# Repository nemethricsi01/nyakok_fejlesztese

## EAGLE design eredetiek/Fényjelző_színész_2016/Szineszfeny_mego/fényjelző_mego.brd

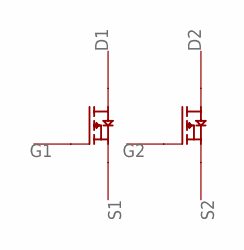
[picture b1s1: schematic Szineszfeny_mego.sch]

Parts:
D1, D2: PADSMD_KICSI; PAD_SMD_KICSI
G1, G2: PADSMD_KICSI; PAD_SMD_KICSI
S1, S2: PADSMD_KICSI; PAD_SMD_KICSI
U$1: AP2625GY-HF-3SOT26; SOT26

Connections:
unnamed: G1.P$4, U$1.P$1 (G)
unnamed: S1.P$4, U$1.P$5 (S)
unnamed: D1.P$4, U$1.P$6 (D)
unnamed: G2.P$4, U$1.P$3 (G)
unnamed: S2.P$4, U$1.P$2 (S)
unnamed: D2.P$4, U$1.P$4 (D)

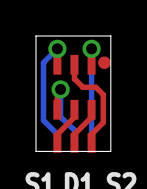
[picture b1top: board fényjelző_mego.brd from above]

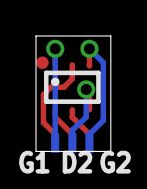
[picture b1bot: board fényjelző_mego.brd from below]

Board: 2 copper layers, 4.2 x 6.4 mm, 7 parts (3 on the bottom side), 6 nets.

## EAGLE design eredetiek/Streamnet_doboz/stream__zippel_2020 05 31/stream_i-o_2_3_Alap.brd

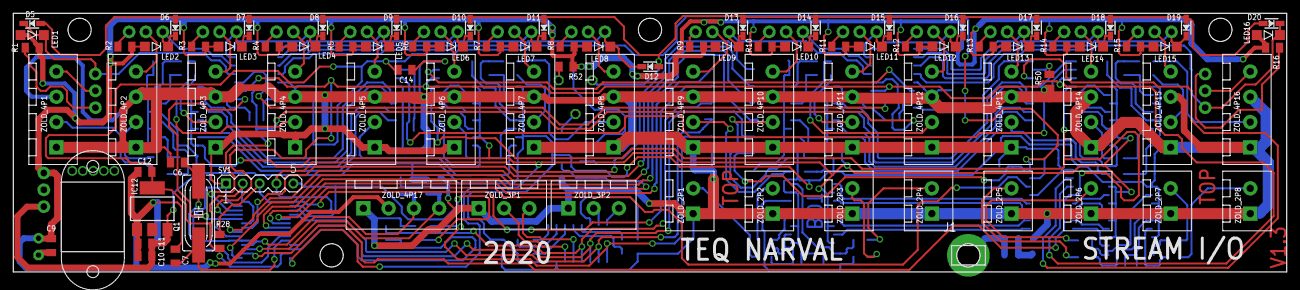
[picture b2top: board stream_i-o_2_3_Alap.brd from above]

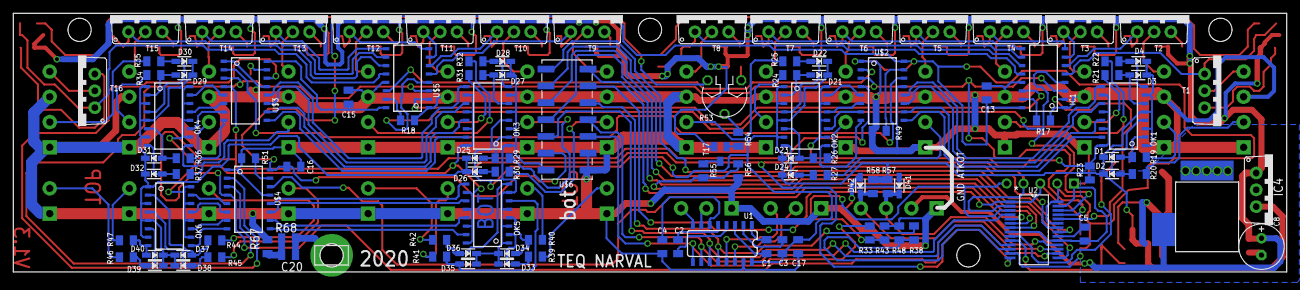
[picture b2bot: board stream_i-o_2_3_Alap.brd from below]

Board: 2 copper layers, 192.0 x 39.0 mm, 200 parts (110 on the bottom side), 174 nets.

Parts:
C1, C2, C3, C4: 1u; C0805
C5, C10, C11, C12: 10u; C0805
C6, C7: 22p; C0805
C8: 220u; E2,5-7
C9, C13, C14, C15, C16, C17, C20: 100n; C0805
D1, D2, D3, D4, D5, D6, D7, D8, D9, D10, D11, D12, D13, D14, D15, D16, D17, D18, D19, D20, D21, D22, D23, D24, D25, D26, D27, D28, D29, D30, D31, D32, D33, D34, D35, D36, D37, D38, D39, D40, D41, D42: 1N4148; SOD-323
DC1: DC_55/21
IC1: SCT21SOP16; SOP16
IC4: 7805TV; TO220V
IC12: LD117AS33TR; SOT223
J1: PIN1-2; 62221
LED1, LED2, LED3, LED4, LED5, LED6, LED7, LED8, LED9, LED10, LED11, LED12, LED13, LED14, LED15, LED16: RED; CHIPLED_1206
OK1, OK2, OK3, OK4, OK5, OK6: TLP281-4; MINI-FLAT-16
Q1: 20MHz; HC49UP
R1, R2, R3, R4, R5, R6, R7, R8, R9, R10, R11, R12, R13, R14, R15, R16: 6R8; R0805
R17, R18, R54, R55, R68: 10k; R0805
R19, R20, R21, R22, R24, R25, R26, R27, R29, R30, R31, R32, R34, R35, R36, R37, R39, R40, R41, R42, R43, R44, R45, R46, R47, R48, R49, R50, R51: 2k2; R0805
R23, R28, R33, R38: 1k; R0805
R52, R57, R58: 4k7; R0805
R53: 10k; PT-6
R56: 3k3; R0805
R67: 100; R0805
SV1: PROG; MA05-1
T1, T2, T3, T4, T5, T6, T7, T8, T9, T10, T11, T12, T13, T14, T15, T16: BD242; TO220V
T17: BC858; SOT23-BEC
U1: MAX232SOIC16; SO016
U2: PIC32MX250F128B-I_SS; SSOP28_MC
U$2, U$3, U$4, U$5: SCT21SOP16; SOP16
U$6: PIN_HEADER_2X7
ZOLD_2P1, ZOLD_2P2, ZOLD_2P3, ZOLD_2P4, ZOLD_2P5, ZOLD_2P6, ZOLD_2P7, ZOLD_2P8: ZOLD_KICSI_2P
ZOLD_3P1, ZOLD_3P2: ZOLD_KICSI_3P
ZOLD_4P1, ZOLD_4P2, ZOLD_4P3, ZOLD_4P4, ZOLD_4P5, ZOLD_4P6, ZOLD_4P7, ZOLD_4P8, ZOLD_4P9, ZOLD_4P10, ZOLD_4P11, ZOLD_4P12, ZOLD_4P13, ZOLD_4P14, ZOLD_4P15, ZOLD_4P16, ZOLD_4P17: ZOLD_KICSI_4P

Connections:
+3V3: C12.1, C13.1, C14.1, C15.1, C16.1, IC1.16, IC12.4, R28.2, SV1.2, U2.13, U2.23, U2.28, U$2.16, U$3.16, U$4.16, U$5.16, U$6.6B
+5V: C3.1, C10.1, C11.1, C17.1, D1.C, D2.C, D3.C, D4.C, D21.C, D22.C, D23.C, D24.C, D25.C, D26.C, D27.C, D28.C, D29.C, D30.C, D31.C, D32.C, D33.C, D34.C, D35.C, D36.C, D37.C, D38.C, D39.C, D40.C, IC4.3, IC12.3, OK1.1, OK1.3, OK1.5, OK1.7, OK2.1, OK2.3, OK2.5, OK2.7, OK3.1, OK3.3, OK3.5, OK3.7, OK4.1, OK4.3, OK4.5, OK4.7, OK5.1, OK5.3, OK5.5, OK5.7, OK6.1, OK6.3, OK6.5, OK6.7, R23.2, R57.2, R58.2, U1.16, U$6.7B
+12V: C8.+, C9.1, DC1.2, IC4.1, LED1.A, LED2.A, LED3.A, LED4.A, LED5.A, LED6.A, LED7.A, LED8.A, LED9.A, LED10.A, LED11.A, LED12.A, LED13.A, LED14.A, LED15.A, LED16.A, R1.2, R2.2, R3.2, R4.2, R5.2, R6.2, R7.2, R8.2, R9.2, R10.2, R11.2, R12.2, R13.2, R14.2, R15.2, R16.2, R52.2, T17.E, ZOLD_4P17.2
CHECK: U2.5, U$4.14
CLK: IC1.3, U2.25, U$2.3, U$3.3, U$4.3, U$5.3
D+: U2.21, U$6.3B
D-: U2.22, U$6.2B
GND: C4.2, C5.2, C6.1, C7.1, C8.-, C9.2, C10.2, C11.2, C12.2, C13.2, C14.2, C15.2, C16.2, C17.2, D41.A, D42.A, DC1.1, IC1.1, IC1.13, IC4.2, IC12.1, R17.1, R18.1, R43.1, R48.1, R49.1, R50.1, R51.1, R56.1, R67.2, SV1.1, U1.15, U2.8, U2.19, U2.27, U$2.1, U$2.13, U$3.1, U$3.13, U$4.1, U$4.13, U$5.1, U$5.13, U$6.6A, U$6.7A, ZOLD_2P1.1, ZOLD_2P2.1, ZOLD_2P3.1, ZOLD_2P4.1, ZOLD_2P5.1, ZOLD_2P6.1, ZOLD_2P7.1, ZOLD_2P8.1, ZOLD_3P1.1, ZOLD_3P2.1, ZOLD_4P1.1, ZOLD_4P1.3, ZOLD_4P2.1, ZOLD_4P2.3, ZOLD_4P3.1, ZOLD_4P3.3, ZOLD_4P4.1, ZOLD_4P4.3, ZOLD_4P5.1, ZOLD_4P5.3, ZOLD_4P6.1, ZOLD_4P6.3, ZOLD_4P7.1, ZOLD_4P7.3, ZOLD_4P8.1, ZOLD_4P8.3, ZOLD_4P9.1, ZOLD_4P9.3, ZOLD_4P10.1, ZOLD_4P10.3, ZOLD_4P11.1, ZOLD_4P11.3, ZOLD_4P12.1, ZOLD_4P12.3, ZOLD_4P13.1, ZOLD_4P13.3, ZOLD_4P14.1, ZOLD_4P14.3, ZOLD_4P15.1, ZOLD_4P15.3, ZOLD_4P16.1, ZOLD_4P16.3, ZOLD_4P17.1
LABE: U2.16, U$2.4, U$3.4, U$4.4
LAKI: IC1.4, U2.26, U$5.4
MCLR: R28.1, SV1.3, U2.1, U$6.2A
unnamed: D8.C, IC1.8, LED4.C, T4.1
unnamed: D5.C, IC1.5, LED1.C, T1.1
unnamed: R1.1, T1.3
unnamed: T1.2, ZOLD_4P1.4
unnamed: D6.C, IC1.6, LED2.C, T2.1
unnamed: R2.1, T2.3
unnamed: T2.2, ZOLD_4P2.4
unnamed: D7.C, IC1.7, LED3.C, T3.1
unnamed: R3.1, T3.3
unnamed: T3.2, ZOLD_4P3.4
unnamed: R4.1, T4.3
unnamed: T4.2, ZOLD_4P4.4
unnamed: D9.C, IC1.9, LED5.C, T5.1
unnamed: R5.1, T5.3
unnamed: T5.2, ZOLD_4P5.4
unnamed: D10.C, IC1.10, LED6.C, T6.1
unnamed: R6.1, T6.3
unnamed: T6.2, ZOLD_4P6.4
unnamed: D11.C, IC1.11, LED7.C, T7.1
unnamed: R7.1, T7.3
unnamed: T7.2, ZOLD_4P7.4
unnamed: D12.C, IC1.12, LED8.C, T8.1
unnamed: R8.1, T8.3
unnamed: T8.2, ZOLD_4P8.4
unnamed: IC1.15, R17.2
unnamed: R18.2, U$5.15
unnamed: IC1.14, U$5.2
unnamed: R20.1, ZOLD_4P1.2
unnamed: D1.A, OK1.2, R19.2
unnamed: R19.1, ZOLD_4P2.2
unnamed: D2.A, OK1.4, R20.2
unnamed: R21.1, ZOLD_4P3.2
unnamed: D13.C, LED9.C, T9.1, U$5.5
unnamed: R9.1, T9.3
unnamed: T9.2, ZOLD_4P9.4
unnamed: D14.C, LED10.C, T10.1, U$5.6
unnamed: R10.1, T10.3
unnamed: T10.2, ZOLD_4P10.4
unnamed: D15.C, LED11.C, T11.1, U$5.7
unnamed: R11.1, T11.3
unnamed: T11.2, ZOLD_4P11.4
unnamed: D16.C, LED12.C, T12.1, U$5.8
unnamed: R12.1, T12.3
unnamed: T12.2, ZOLD_4P12.4
unnamed: D17.C, LED13.C, T13.1, U$5.9
unnamed: R13.1, T13.3
unnamed: T13.2, ZOLD_4P13.4
unnamed: D18.C, LED14.C, T14.1, U$5.10
unnamed: R14.1, T14.3
unnamed: T14.2, ZOLD_4P14.4
unnamed: D19.C, LED15.C, T15.1, U$5.11
unnamed: R15.1, T15.3
unnamed: T15.2, ZOLD_4P15.4
unnamed: D20.C, LED16.C, T16.1, U$5.12
unnamed: R16.1, T16.3
unnamed: T16.2, ZOLD_4P16.4
unnamed: D3.A, OK1.6, R21.2
unnamed: R22.1, ZOLD_4P4.2
unnamed: D4.A, OK1.8, R22.2
unnamed: R35.1, ZOLD_4P16.2
unnamed: D5.A, D6.A, D7.A, D8.A, D9.A, D10.A, D11.A, D12.A, D13.A, D14.A, D15.A, D16.A, D17.A, D18.A, D19.A, D20.A, R53.E
unnamed: D25.A, OK3.2, R29.2
unnamed: D26.A, OK3.4, R30.2
unnamed: OK1.15, U$2.9
unnamed: OK1.13, U$2.10
unnamed: OK1.11, U$2.11
unnamed: OK1.9, U$2.12
unnamed: D21.A, OK2.2, R24.2
unnamed: D22.A, OK2.4, R25.2
unnamed: D23.A, OK2.6, R26.2
unnamed: D24.A, OK2.8, R27.2
unnamed: R25.1, ZOLD_4P8.2
unnamed: R24.1, ZOLD_4P7.2
unnamed: R26.1, ZOLD_4P6.2
unnamed: R27.1, ZOLD_4P5.2
unnamed: OK5.15, U$4.9
unnamed: OK2.15, U$2.5
unnamed: OK2.13, U$2.6
unnamed: OK2.11, U$2.7
unnamed: OK2.9, U$2.8
unnamed: D27.A, OK3.6, R31.2
unnamed: D28.A, OK3.8, R32.2
unnamed: R30.1, ZOLD_4P9.2
unnamed: R29.1, ZOLD_4P10.2
unnamed: R31.1, ZOLD_4P11.2
unnamed: R32.1, ZOLD_4P12.2
unnamed: R34.1, ZOLD_4P15.2
unnamed: OK3.15, U$3.9
unnamed: OK3.13, U$3.10
unnamed: OK3.11, U$3.11
unnamed: OK3.9, U$3.12
unnamed: D29.A, OK4.2, R34.2
unnamed: D30.A, OK4.4, R35.2
unnamed: D31.A, OK4.6, R36.2
unnamed: D32.A, OK4.8, R37.2
unnamed: OK5.13, U$4.10
unnamed: R36.1, ZOLD_4P14.2
unnamed: R37.1, ZOLD_4P13.2
unnamed: OK5.11, U$4.11
unnamed: OK4.15, U$3.5
unnamed: OK4.13, U$3.6
unnamed: OK4.11, U$3.7
unnamed: OK4.9, U$3.8
unnamed: D33.A, OK5.2, R39.2
unnamed: D34.A, OK5.4, R40.2
unnamed: D35.A, OK5.6, R41.2
unnamed: D36.A, OK5.8, R42.2
unnamed: R39.1, ZOLD_2P1.2
unnamed: R40.1, ZOLD_2P2.2
unnamed: R41.1, ZOLD_2P3.2
unnamed: R42.1, ZOLD_2P4.2
unnamed: OK5.9, U$4.12
unnamed: R45.1, ZOLD_2P5.2
unnamed: R47.1, ZOLD_2P7.2
unnamed: R44.1, ZOLD_2P6.2
unnamed: R46.1, ZOLD_2P8.2
unnamed: D37.A, OK6.2, R44.2
unnamed: D38.A, OK6.4, R45.2
unnamed: D39.A, OK6.6, R46.2
unnamed: D40.A, OK6.8, R47.2
unnamed: C1.2, U1.3
unnamed: C1.1, U1.1
unnamed: C2.1, U1.4
unnamed: C2.2, U1.5
unnamed: C3.2, U1.2
unnamed: OK6.15, U$4.5
unnamed: OK6.13, U$4.6
unnamed: OK6.11, U$4.7
unnamed: OK6.9, U$4.8
unnamed: R51.2, U$4.15
unnamed: R50.2, U$3.15
unnamed: R49.2, U$2.15
unnamed: U$2.2, U$5.14
unnamed: U$2.14, U$3.2
unnamed: U$3.14, U$4.2
unnamed: U1.14, ZOLD_3P1.2
unnamed: C4.1, U1.6
unnamed: U1.13, ZOLD_3P1.3
unnamed: U1.7, ZOLD_3P2.2
unnamed: U1.8, ZOLD_3P2.3
unnamed: C5.1, U2.20
unnamed: C20.1, R67.1, R68.2
unnamed: R52.1, R53.A
unnamed: R53.S, R54.2
unnamed: R54.1, T17.B
unnamed: C20.2, J1.1, R68.1
unnamed: R55.2, T17.C
unnamed: C7.2, Q1.1, U2.10
unnamed: C6.2, Q1.2, U2.9
OVER_CURRENT_IN: R55.1, R56.2, U2.7
PGED: SV1.4, U2.2, U$6.1B
POWER: U2.6, U$6.1A
SCL1: D42.C, R58.1, U2.17, ZOLD_4P17.4
SDA1: D41.C, R57.1, U2.18, ZOLD_4P17.3
SDI1: OK1.10, OK1.12, OK1.14, OK1.16, OK2.10, OK2.12, OK2.14, OK2.16, OK3.10, OK3.12, OK3.14, OK3.16, OK4.10, OK4.12, OK4.14, OK4.16, OK5.10, OK5.12, OK5.14, OK5.16, OK6.10, OK6.12, OK6.14, OK6.16, R23.1, U2.14
SDO1: IC1.2, U2.24
U1RX: R38.1, R48.2, U2.12
U1RX_5V: R38.2, U1.12, U$6.3A
U1TX: U1.11, U2.11, U$6.5B
U2RX: R33.1, R43.2, SV1.5, U2.3
U2RX_5V: R33.2, U1.9, U$6.5A
U2TX: U1.10, U2.4, U$6.4A
VBUS: U2.15, U$6.4B

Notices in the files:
parts and their libraries:
microbuilder: This work is placed in the public domain, and may be freely used for commercial and non-commercial work with the following conditions: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
SparkFun-DigitalIC: Licensing: Creative Commons ShareAlike 4.0 International - https://creativecommons.org/licenses/by-sa/4.0
